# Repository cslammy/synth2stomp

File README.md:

# synth2stomp
Files for the "synth2stomp" blog post

NOTE: this is my own circuit design based on Ken Stone/Elby CGS360.  This is not a PCB for the CGS360
Also: this board is for Frak or large format; not for Eurorack.

https://audiodiwhy.blogspot.com/2020/10/stomp-synth-adapter-all-hail-ken-stone.html

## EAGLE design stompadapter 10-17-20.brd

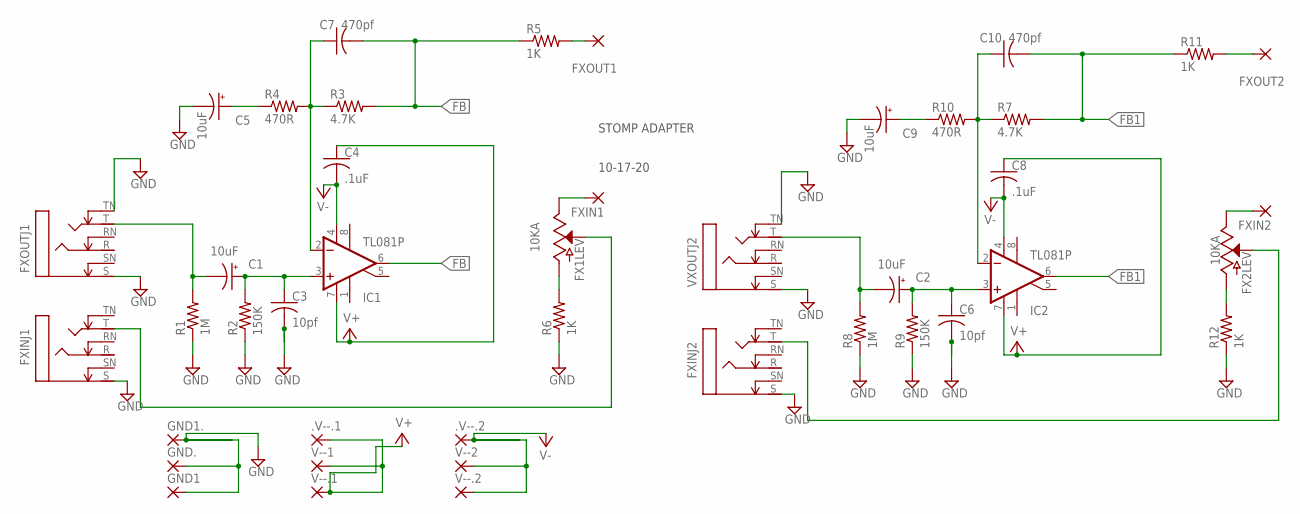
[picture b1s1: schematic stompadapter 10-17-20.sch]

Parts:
.V--.1, .V--.2: 3,17/1,3
C1, C2, C5, C9: 10uF; E5-6
C3, C6: 10pf; C050-025X075
C4, C8: .1uF; C025-025X050
C7, C10: 470pf; C050-025X075
FX1LEV, FX2LEV: 10KA; POT-PTH-ALPS-KIT
FXIN1, FXIN2: 3,17/1,3
FXINJ1, FXINJ2: NEUTRIXNMJ6HCD2; NMJ6HCD2-LARGEPINS
FXOUT1, FXOUT2: 3,17/1,3
FXOUTJ1: NEUTRIXNMJ6HCD2; NMJ6HCD2-LARGEPINS
GND1, GND1., GND.: 3,17/1,3
IC1, IC2: TL081P; DIL08
R1, R8: 1M; 0204/7
R2, R9: 150K; 0204/7
R3, R7: 4.7K; 0204/7
R4, R10: 470R; 0204/7
R5, R6, R11, R12: 1K; 0204/7
V--1, V--2, V--.1, V--.2: 3,17/1,3
VXOUTJ2: NEUTRIXNMJ6HCD2; NMJ6HCD2-LARGEPINS

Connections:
FB: C7.2, IC1.6 (OUT), R3.2, R5.1
FB1: C10.2, IC2.6 (OUT), R7.2, R11.1
GND: C3.2, C5.-, C6.2, C9.-, FXINJ1.S, FXINJ2.S, FXOUTJ1.S, FXOUTJ1.TN, GND1.1, GND1..1, GND..1, R1.1, R2.1, R6.1, R8.1, R9.1, R12.1, VXOUTJ2.S, VXOUTJ2.TN
unnamed: C1.+, C3.1, IC1.3 (+IN), R2.2
unnamed: C1.-, FXOUTJ1.T, R1.2
unnamed: FXOUT1.1, R5.2
unnamed: C5.+, R4.1
unnamed: C7.1, IC1.2 (-IN), R3.1, R4.2
unnamed: FX1LEV.P$1 (E), FXIN1.1
unnamed: FX1LEV.P$3 (A), R6.2
unnamed: FX1LEV.P$2 (S), FXINJ1.T
unnamed: C2.+, C6.1, IC2.3 (+IN), R9.2
unnamed: C2.-, R8.2, VXOUTJ2.T
unnamed: FXOUT2.1, R11.2
unnamed: C9.+, R10.1
unnamed: C10.1, IC2.2 (-IN), R7.1, R10.2
unnamed: FX2LEV.P$1 (E), FXIN2.1
unnamed: FX2LEV.P$3 (A), R12.2
unnamed: FX2LEV.P$2 (S), FXINJ2.T
V+: .V--.1.1, C4.1, C8.1, IC1.7 (V+), IC2.7 (V+), V--1.1, V--.1.1
V-: .V--.2.1, C4.2, C8.2, IC1.4 (V-), IC2.4 (V-), V--2.1, V--.2.1

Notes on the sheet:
STOMP ADAPTER
10-17-20

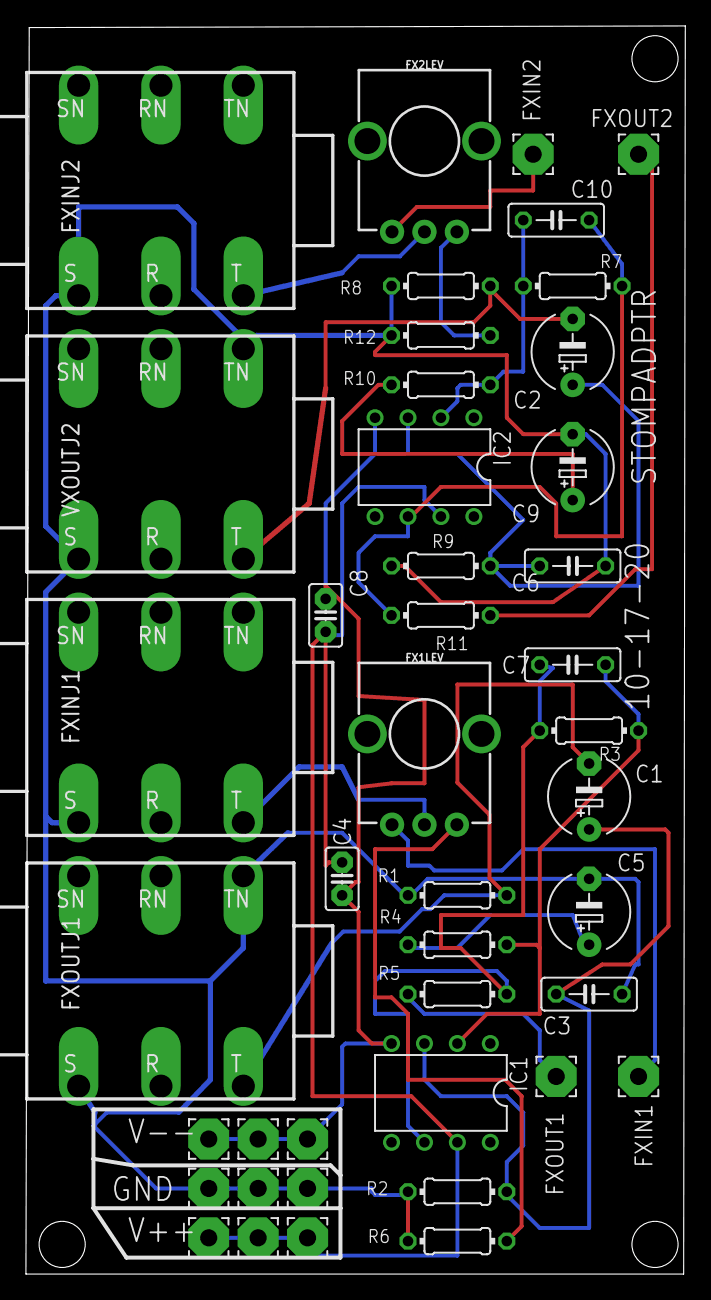
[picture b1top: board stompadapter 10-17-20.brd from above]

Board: 2 copper layers, 50.9 x 96.3 mm, 43 parts (0 on the bottom side), 21 nets.

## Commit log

2024-10-30 Added Eagle files
    See blog post https://audiodiwhy.blogspot.com/2020/10/stomp-synth-adapter-all-hail-ken-stone.html
2024-10-30 added gerber

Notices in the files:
parts and their libraries:
SparkFun-Resistors: Licensing: Creative Commons ShareAlike 4.0 International - https://creativecommons.org/licenses/by-sa/4.0
